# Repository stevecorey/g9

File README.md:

# g9

Webpage and repository for ECE 3992 Spring 2018 Group 9 project

# [Project Proposal](https://github.com/stevecorey/g9/tree/master/proposal)

## [Meeting Log](https://drive.google.com/open?id=1EqHrG5070RBNwIU5UX6c98iH-gWA2iIF8dvR4XRqYG4)

[Mission statement](https://goo.gl/5UtYJM)

[Abstract](https://drive.google.com/open?id=1ATABZSRttfmpXNOQQWVi6gUUWrG7QBtsrjB3JEH96ko)

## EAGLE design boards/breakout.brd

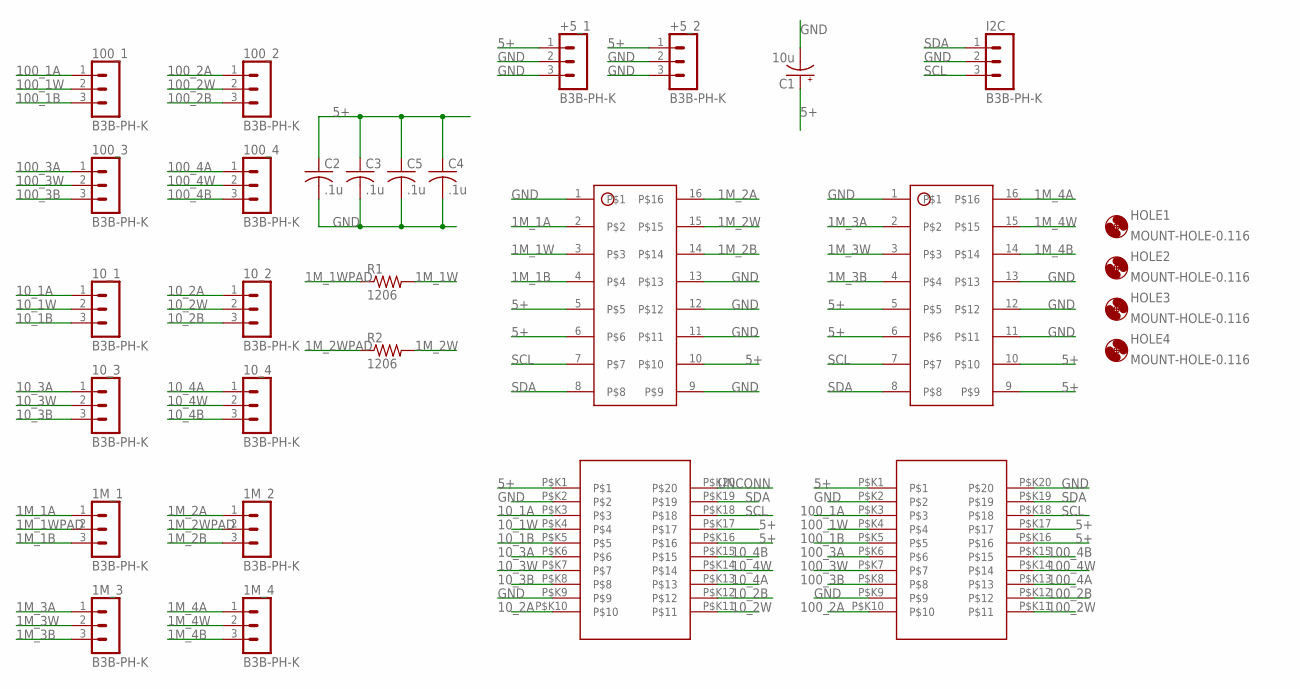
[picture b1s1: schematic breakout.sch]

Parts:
1M_1, 1M_2, 1M_3, 1M_4, 10_1, 10_2, 10_3, 10_4, 100_1, 100_2, 100_3, 100_4: B3B-PH-K
10K, 100K: TSSOP20
+5_1, +5_2: B3B-PH-K
C1: 10u; E3,5-8
C2, C3, C4, C5: .1u; C1206K
HOLE1, HOLE2, HOLE3, HOLE4: MOUNT-HOLE-0.116; 116
I2C: B3B-PH-K
MEG_1, MEG_2: SOIC-16; SOIC127P600X175-16N
R1, R2: 1206; R1206

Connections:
1M_1A: 1M_1.1, MEG_1.2
1M_1B: 1M_1.3, MEG_1.4
1M_1W: MEG_1.3, R1.2
1M_1WPAD: 1M_1.2, R1.1
1M_2A: 1M_2.1, MEG_1.16
1M_2B: 1M_2.3, MEG_1.14
1M_2W: MEG_1.15, R2.2
1M_2WPAD: 1M_2.2, R2.1
1M_3A: 1M_3.1, MEG_2.2
1M_3B: 1M_3.3, MEG_2.4
1M_3W: 1M_3.2, MEG_2.3
1M_4A: 1M_4.1, MEG_2.16
1M_4B: 1M_4.3, MEG_2.14
1M_4W: 1M_4.2, MEG_2.15
5+: 10K.P$K1, 10K.P$K16, 10K.P$K17, 100K.P$K1, 100K.P$K16, 100K.P$K17, +5_1.1, +5_2.1, C1.+, C2.1, C3.1, C4.1, C5.1, MEG_1.5, MEG_1.6, MEG_1.10, MEG_2.5, MEG_2.6, MEG_2.9, MEG_2.10
10_1A: 10K.P$K3, 10_1.1
10_1B: 10K.P$K5, 10_1.3
10_1W: 10K.P$K4, 10_1.2
10_2A: 10K.P$K10, 10_2.1
10_2B: 10K.P$K12, 10_2.3
10_2W: 10K.P$K11, 10_2.2
10_3A: 10K.P$K6, 10_3.1
10_3B: 10K.P$K8, 10_3.3
10_3W: 10K.P$K7, 10_3.2
10_4A: 10K.P$K13, 10_4.1
10_4B: 10K.P$K15, 10_4.3
10_4W: 10K.P$K14, 10_4.2
100_1A: 100K.P$K3, 100_1.1
100_1B: 100K.P$K5, 100_1.3
100_1W: 100K.P$K4, 100_1.2
100_2A: 100K.P$K10, 100_2.1
100_2B: 100K.P$K12, 100_2.3
100_2W: 100K.P$K11, 100_2.2
100_3A: 100K.P$K6, 100_3.1
100_3B: 100K.P$K8, 100_3.3
100_3W: 100K.P$K7, 100_3.2
100_4A: 100K.P$K13, 100_4.1
100_4B: 100K.P$K15, 100_4.3
100_4W: 100K.P$K14, 100_4.2
GND: 10K.P$K2, 10K.P$K9, 100K.P$K2, 100K.P$K9, 100K.P$K20, +5_1.2, +5_1.3, +5_2.2, +5_2.3, C1.-, C2.2, C3.2, C4.2, C5.2, I2C.2, MEG_1.1, MEG_1.9, MEG_1.11, MEG_1.12, MEG_1.13, MEG_2.1, MEG_2.11, MEG_2.12, MEG_2.13
SCL: 10K.P$K18, 100K.P$K18, I2C.3, MEG_1.7, MEG_2.7
SDA: 10K.P$K19, 100K.P$K19, I2C.1, MEG_1.8, MEG_2.8
UNCONN: 10K.P$K20

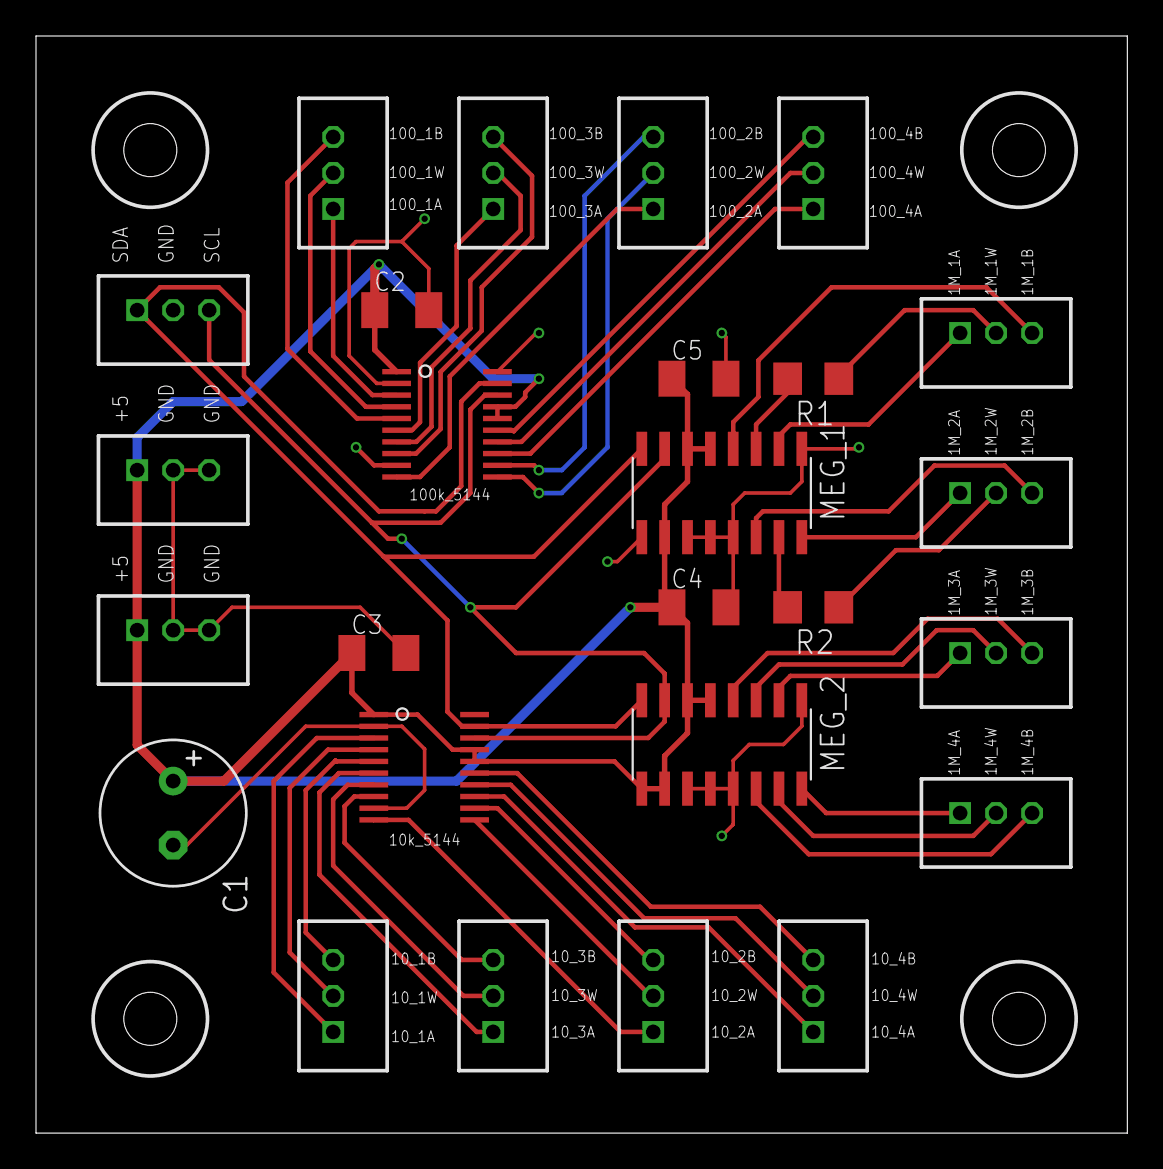
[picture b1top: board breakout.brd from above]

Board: 2 copper layers, 60.6 x 61.0 mm, 30 parts (0 on the bottom side), 42 nets.

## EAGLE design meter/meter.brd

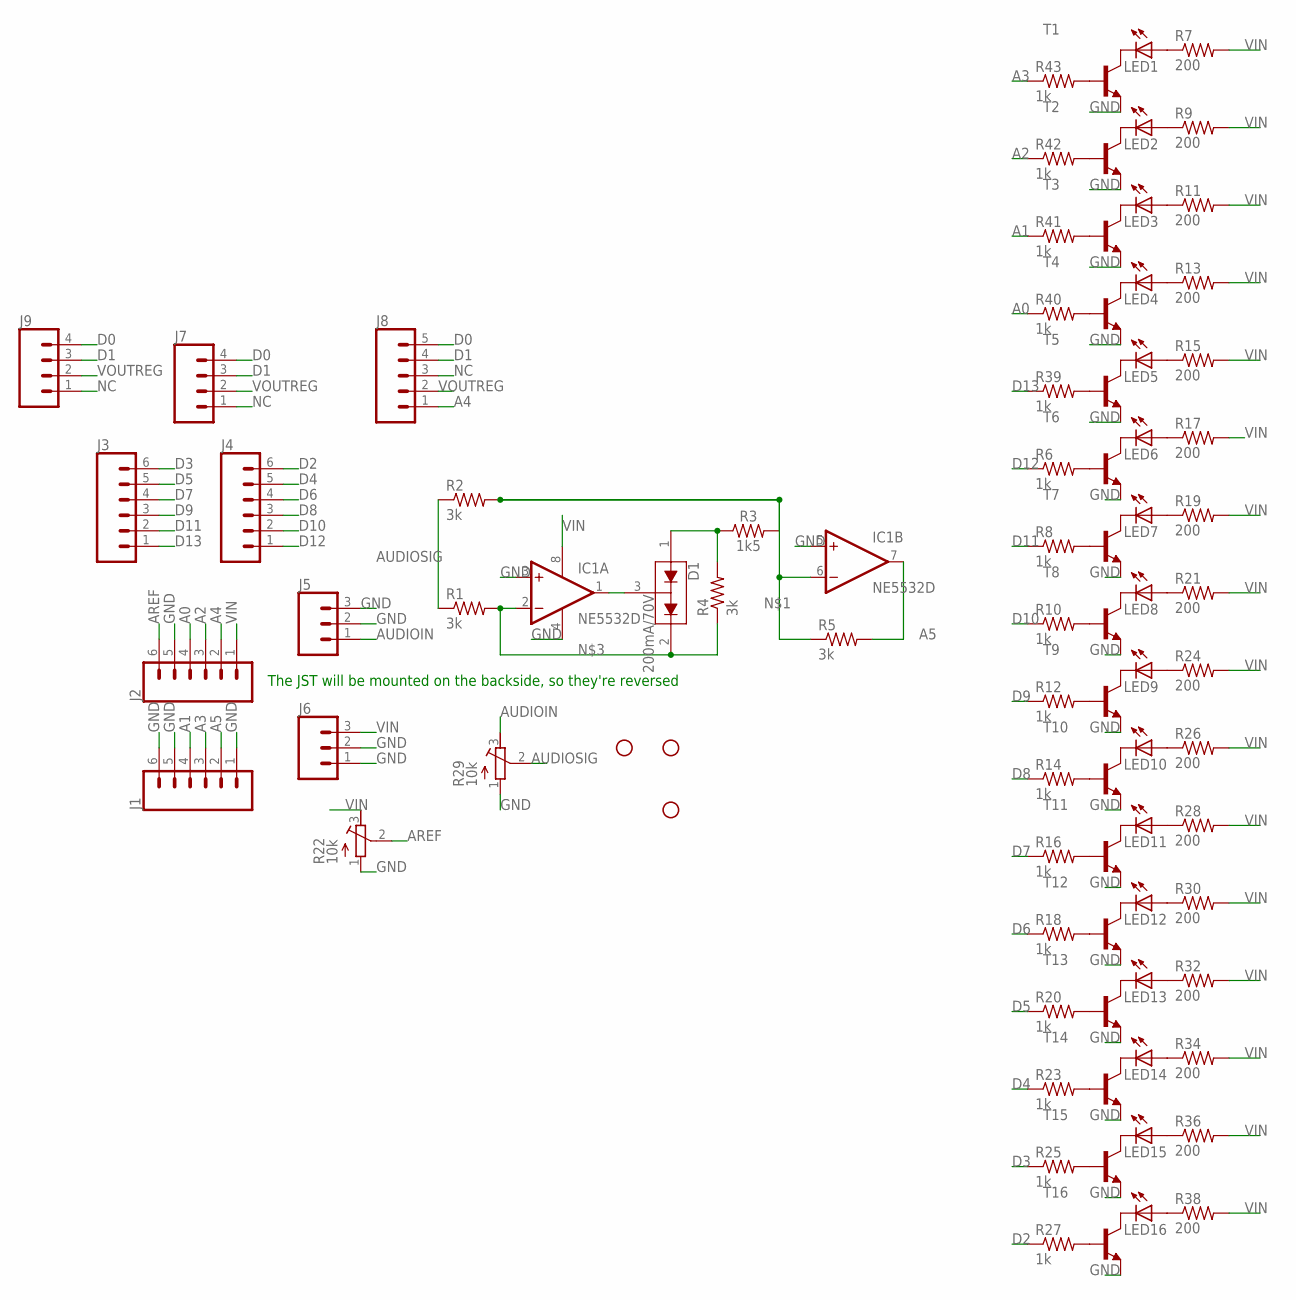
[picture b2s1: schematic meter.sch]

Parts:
D1: 200mA/70V; SOT23-3
H1, H2, H4: STAND-OFF
IC1: NE5532D; SO08
J1, J2, J3, J4: CONN_061.27MM; 1X06_1.27MM
J5, J6: CONN_03JST-PTH-VERT; JST-3-PTH-VERT
J7, J9: CONN_041.27MM; 1X04_1.27MM
J8: CONN_05NO_SILK; 1X05_NO_SILK
LED1, LED2, LED3, LED4, LED5, LED6, LED7, LED8, LED9, LED10, LED11, LED12, LED13, LED14, LED15, LED16: LEDCHIP-LED0805; CHIP-LED0805
R1, R2, R4, R5: 3k; R0805
R3: 1k5; 1206
R6, R8, R10, R12, R14, R16, R18, R20, R23, R25, R27, R39, R40, R41, R42, R43: 1k; R0805
R7, R9, R11, R13, R15, R17, R19, R21, R24, R26, R28, R30, R32, R34, R36, R38: 200; R0805
R22, R29: 10k; RTRIM3296Y
T1, T2, T3, T4, T5, T6, T7, T8, T9, T10, T11, T12, T13, T14, T15, T16: BCX56-NPN-SOT89-BCE; SOT89-BCE

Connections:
A0: J2.4, R40.1
A1: J1.4, R41.1
A2: J2.3, R42.1
A3: J1.3, R43.1
A4: J2.2, J8.1
A5: IC1.7 (OUT), J1.2, R5.2
AREF: J2.6, R22.2 (S)
AUDIOIN: J5.1, R29.3 (E)
AUDIOSIG: R1.1, R2.1, R29.2 (S)
D0: J7.4, J8.5, J9.4
D1: J7.3, J8.4, J9.3
D2: J4.6, R27.1
D3: J3.6, R25.1
D4: J4.5, R23.1
D5: J3.5, R20.1
D6: J4.4, R18.1
D7: J3.4, R16.1
D8: J4.3, R14.1
D9: J3.3, R12.1
D10: J4.2, R10.1
D11: J3.2, R8.1
D12: J4.1, R6.1
D13: J3.1, R39.1
GND: IC1.3 (+IN), IC1.4 (V-), IC1.5 (+IN), J1.1, J1.5, J1.6, J2.5, J5.2, J5.3, J6.1, J6.2, R22.1 (A), R29.1 (A), T1.E, T2.E, T3.E, T4.E, T5.E, T6.E, T7.E, T8.E, T9.E, T10.E, T11.E, T12.E, T13.E, T14.E, T15.E, T16.E
unnamed: IC1.6 (-IN), R2.2, R3.2, R5.1
unnamed: D1.3 (COM), IC1.1 (OUT)
unnamed: D1.2 (C2), IC1.2 (-IN), R1.2, R4.1
unnamed: D1.1 (A1), R3.1, R4.2
unnamed: R43.2, T1.B
unnamed: LED1.C, T1.C
unnamed: LED1.A, R7.1
unnamed: LED2.C, T2.C
unnamed: LED2.A, R9.1
unnamed: R42.2, T2.B
unnamed: LED3.C, T3.C
unnamed: LED3.A, R11.1
unnamed: R41.2, T3.B
unnamed: LED4.C, T4.C
unnamed: LED4.A, R13.1
unnamed: R40.2, T4.B
unnamed: LED5.C, T5.C
unnamed: LED5.A, R15.1
unnamed: R39.2, T5.B
unnamed: LED6.C, T6.C
unnamed: LED6.A, R17.1
unnamed: R6.2, T6.B
unnamed: LED7.C, T7.C
unnamed: LED7.A, R19.1
unnamed: R8.2, T7.B
unnamed: LED8.C, T8.C
unnamed: LED8.A, R21.1
unnamed: R10.2, T8.B
unnamed: LED9.C, T9.C
unnamed: LED9.A, R24.1
unnamed: R12.2, T9.B
unnamed: LED10.C, T10.C
unnamed: LED10.A, R26.1
unnamed: R14.2, T10.B
unnamed: LED11.C, T11.C
unnamed: LED11.A, R28.1
unnamed: R16.2, T11.B
unnamed: LED12.C, T12.C
unnamed: LED12.A, R30.1
unnamed: R18.2, T12.B
unnamed: LED13.C, T13.C
unnamed: LED13.A, R32.1
unnamed: R20.2, T13.B
unnamed: LED14.C, T14.C
unnamed: LED14.A, R34.1
unnamed: R23.2, T14.B
unnamed: LED15.C, T15.C
unnamed: LED15.A, R36.1
unnamed: R25.2, T15.B
unnamed: LED16.C, T16.C
unnamed: LED16.A, R38.1
unnamed: R27.2, T16.B
NC: J7.1, J8.3, J9.1
VIN: IC1.8 (V+), J2.1, J6.3, R7.2, R9.2, R11.2, R13.2, R15.2, R17.2, R19.2, R21.2, R22.3 (E), R24.2, R26.2, R28.2, R30.2, R32.2, R34.2, R36.2, R38.2
VOUTREG: J7.2, J8.2, J9.2

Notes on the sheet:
The JST will be mounted on the backside, so they're reversed

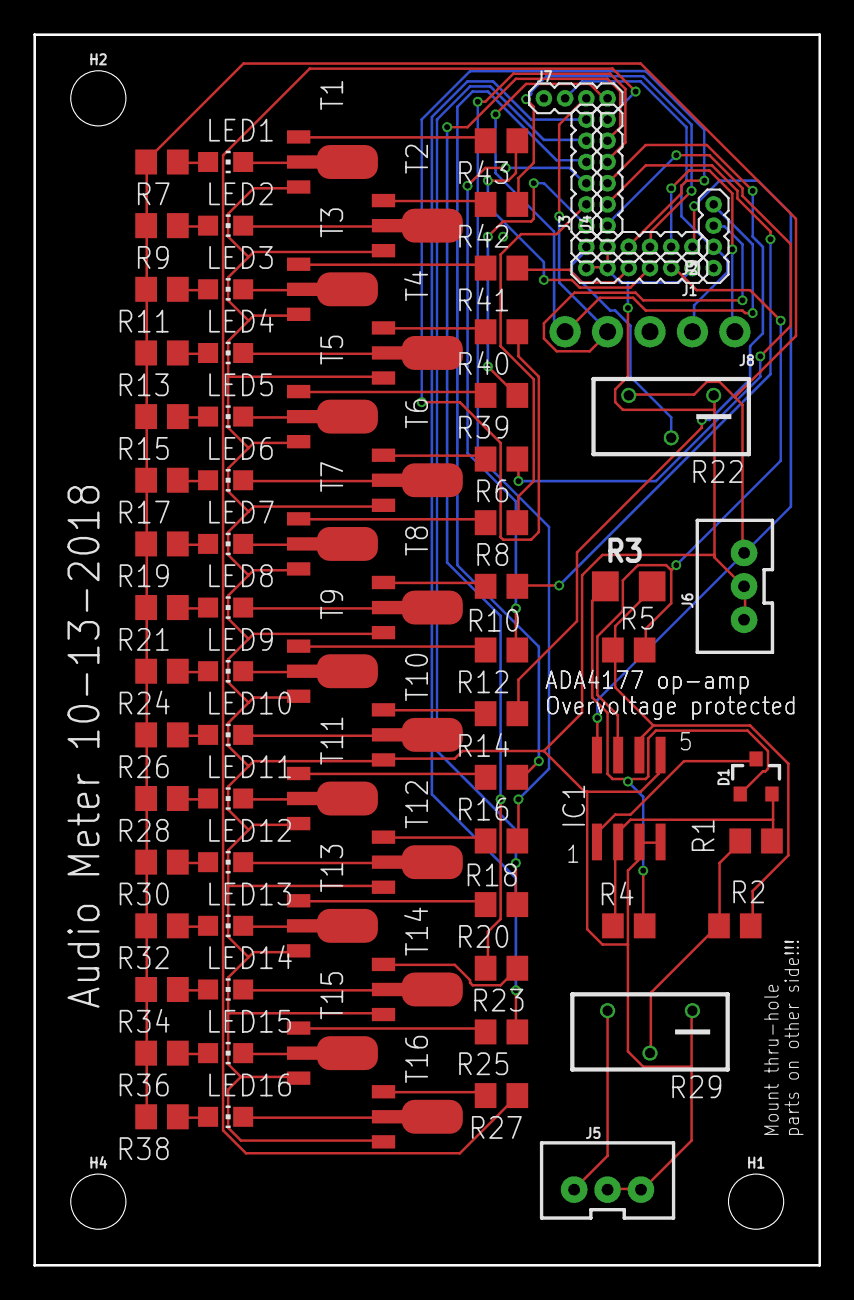
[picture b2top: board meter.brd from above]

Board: 2 copper layers, 47.0 x 73.7 mm, 85 parts (0 on the bottom side), 79 nets.

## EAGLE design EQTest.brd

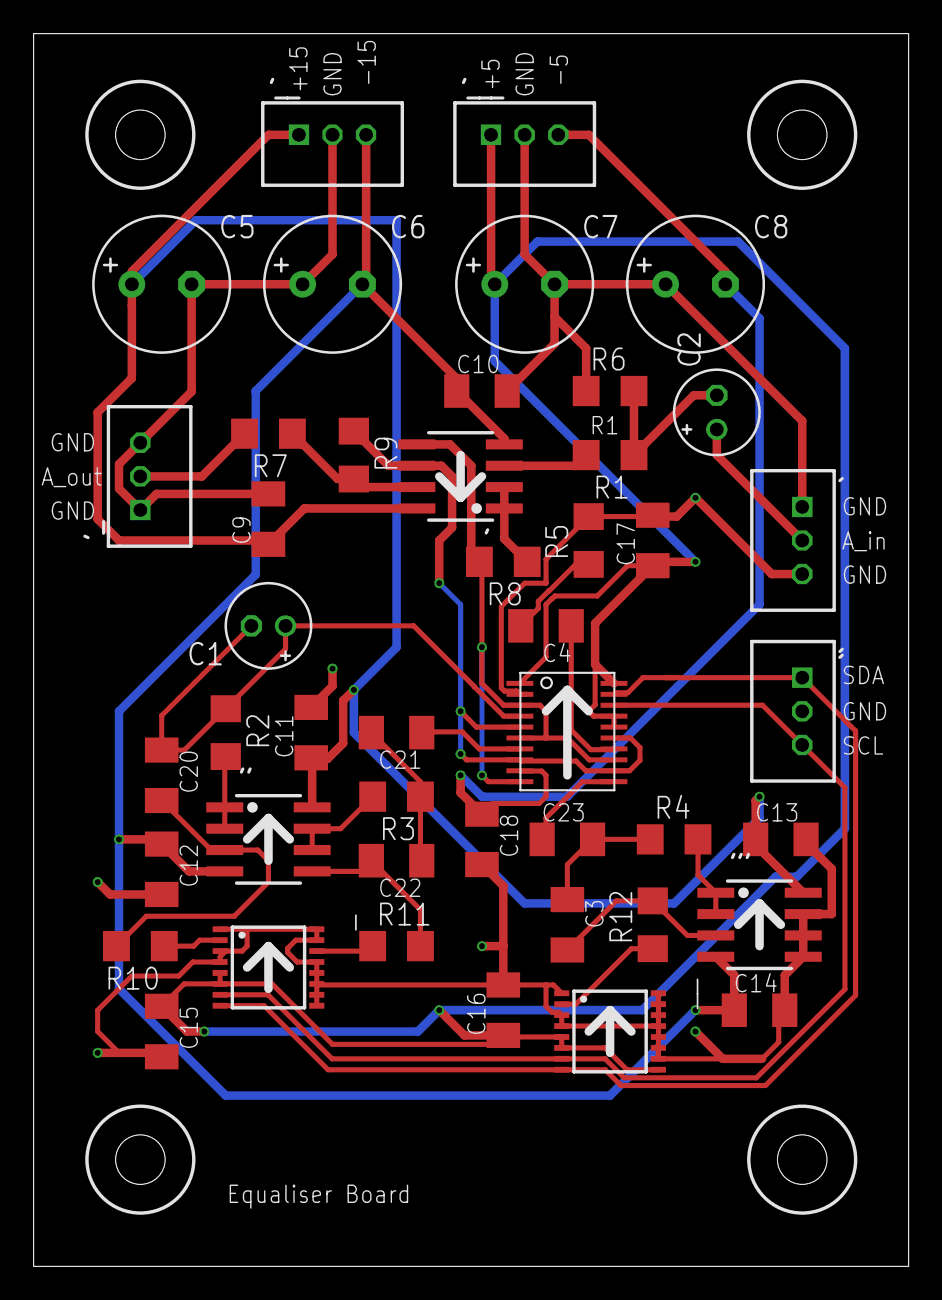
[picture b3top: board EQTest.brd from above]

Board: 2 copper layers, 52.0 x 73.3 mm, 49 parts (0 on the bottom side), 31 nets.

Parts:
10K: TSSOP20
': NE5532; SO08
'': NE5532; SO08
''': NE5532; SO08
'_: B3B-PH-K
'__: B3B-PH-K
'___: B3B-PH-K
C1, C2: 1uF; E2-5
C3, C4: 10nF; C1206K
C5, C6, C7, C8: 10uF; E3,5-8
C9, C10, C11, C12, C13, C14, C15, C16, C17, C18: 100nF; C1206K
C20: 47nF; C1206K
C21: 150nF; C1206K
C22, C23: 22nF; C1206K
HOLE1, HOLE2, HOLE3, HOLE4: MOUNT-HOLE-0.116; 116
R1, R2, R3, R4, R5: 470; R1206
R6: 100K; R1206
R7: 100; R1206
R8, R9: 2.7K; R1206
R10, R11, R12: 47K; R1206
_: AD5242; TSSOP16
__: AD5242; TSSOP16
`: B3B-PH-K
``: B3B-PH-K

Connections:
5+: 10K.P$K1, 10K.P$K16, 10K.P$K17, 10K.P$K20, '___.1, C7.+, C15.1, C16.1, C17.1, _.5, _.6, __.5, __.6, __.9
5-: 10K.P$K9, '___.3, C8.-, C18.1
15+: '.8, ''.8, '''.8, '__.1, C5.+, C9.1, C11.1, C13.1
15-: '.4, ''.4, '''.4, '__.3, C6.-, C10.1, C12.1, C14.1
AD5144: 10K.P$K3, 10K.P$K6, 10K.P$K10, 10K.P$K13, '.5, R8.2
AUDIO_IN: C2.+, `.2
AUDIO_OUT: '_.2, R7.2
BASS+: ''.3, C20.2, R10.2
BASS_10: 10K.P$K4, C1.+, C1.-, C20.1, R2.1
BASS_MEG: R10.1, _.2
BASS_OUT: ''.1, ''.2, R2.2
GROUND: 10K.P$K2, '''.5, '''.6, '''.7, '_.1, '_.3, '__.2, '___.2, C5.-, C6.+, C7.-, C8.+, C9.2, C10.2, C11.2, C12.2, C13.2, C14.2, C15.2, C16.2, C17.2, C18.2, R5.2, R6.1, _.1, _.3, _.4, _.9, _.10, _.11, _.12, _.13, _.15, _.16, __.1, __.3, __.4, __.10, __.11, __.12, __.13, __.14, __.15, __.16, `.1, `.3, ``.2
HIGH+: '''.3, C3.2, R12.2
HIGH_10: 10K.P$K11, C23.1
HIGH_MEG: R12.1, __.2
HIGH_OUT: '''.1, '''.2, R4.2
IN+: '.3, R1.2
IN_OUT: '.1, '.2, R8.1
LOW+: ''.5, C22.2, R11.2
LOW_10: 10K.P$K7, C21.1
LOW_MEG: R11.1, _.14
LOW_OUT: ''.6, ''.7, R3.2
unnamed: C4.2, R5.1
unnamed: C3.1, C23.2, R4.1
unnamed: C21.2, C22.1, R3.1
unnamed: C2.-, R1.1, R6.2
OUT-: 10K.P$K5, 10K.P$K8, 10K.P$K12, 10K.P$K15, '.6, R9.1
OUT_OUT: '.7, R7.1, R9.2
SCL: 10K.P$K18, _.7, __.7, ``.3
SDA: 10K.P$K19, _.8, __.8, ``.1
TREBLE_10: 10K.P$K14, C4.1

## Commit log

2018-02-22 url test
2018-02-22 added meeting notes
2018-02-22 added abstract
2018-02-22 changed meeting notes link
2018-02-22 clarified content
2018-04-30 initial import
2018-04-30 just backing up
2018-04-30 edits
2018-05-01 milestones added
2018-05-01 Added proposal doc
2018-08-23 Added EQ parts list
2018-08-24 added purchase links
2018-09-06 Added the EQ board file
2018-10-30 Added breakout board file and the i2c functions
2018-11-09 added meter PCB
2018-11-27 Added the Rotary Encoder files
2018-11-27 renamed meter -> rotaryEnc
2018-11-29 Fixed i2cFunctions.py
2018-12-07 Added RotEnc code
2018-12-08 fixed a part of the rotEnc code
2018-12-17 included necessary files, and reorganized
2018-12-29 wood laser note

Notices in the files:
parts and their libraries:
con-jst-ph: Copyright (C) 2016, Bob Starr
ne5532: Copyright (C) 2006 by Bob Starr
SparkFun-DiscreteSemi: Licensing: Creative Commons ShareAlike 4.0 International - https://creativecommons.org/licenses/by-sa/4.0
